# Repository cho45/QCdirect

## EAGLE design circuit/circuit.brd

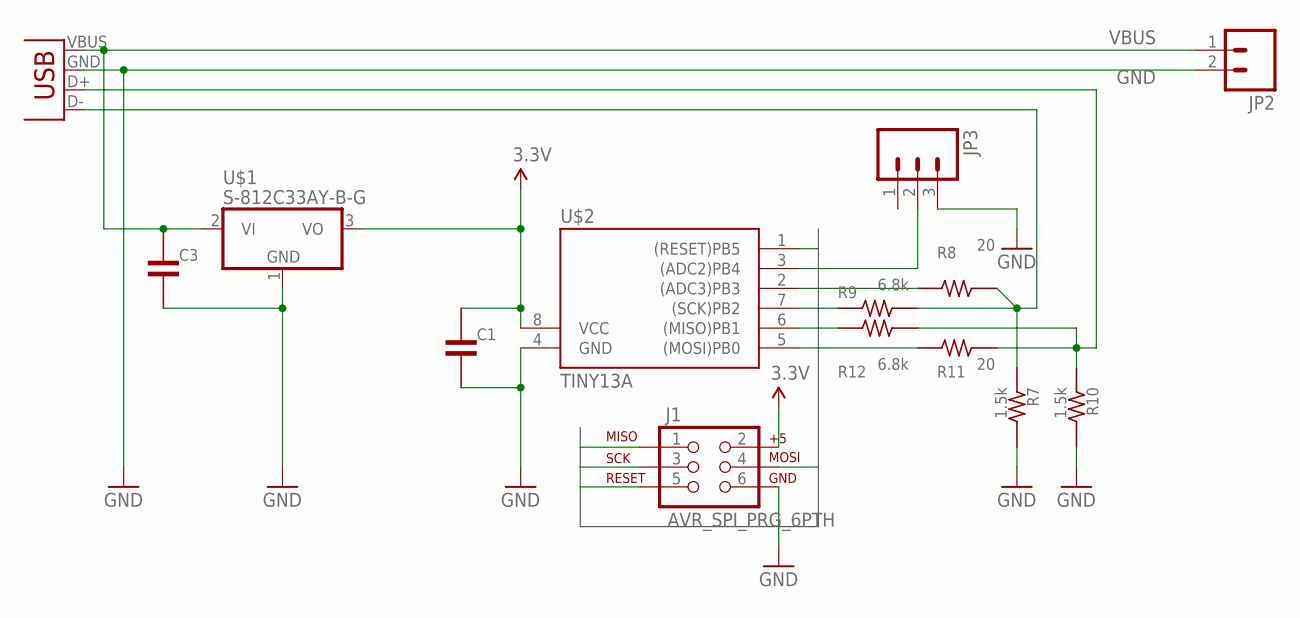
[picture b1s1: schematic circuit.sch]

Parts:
C1, C3: C-50V-0302-2.54; 50-0302-2.54
J1: AVR_SPI_PRG_6PTH; 2X3
JP1: USB-A-H
JP2: M02PTH; 1X02
JP3: M03PTH; 1X03
R7, R10: 1.5k; 1/4W-5.08V
R8, R11: 20; 1/4W-5.08V
R9, R12: 6.8k; 1/4W-5.08V
U$1: S-812C33AY-B-G; TO-92
U$2: TINY13A; DIL08

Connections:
0.6V2: JP1.D- (D+), R7.PAD1 (1), R8.PAD2 (2), R9.PAD2 (2)
0.6V3: JP1.D+ (D-), R10.PAD1 (1), R11.PAD2 (2), R12.PAD2 (2)
3.3V: C1.PAD1 (1), J1.2, U$1.3 (VO), U$2.8 (VCC)
GND: C1.PAD2 (2), C3.PAD2 (2), J1.6, JP1.GND (VBUS), JP2.2, JP3.3, R7.PAD2 (2), R10.PAD2 (2), U$1.1 (GND), U$2.4 (GND)
MISO: J1.1, R12.PAD1 (1), U$2.6 ((MISO)PB1)
MOSI: J1.4, R11.PAD1 (1), U$2.5 ((MOSI)PB0)
unnamed: R8.PAD1 (1), U$2.2 ((ADC3)PB3)
unnamed: JP3.2, U$2.3 ((ADC2)PB4)
RESET: J1.5, U$2.1 ((RESET)PB5)
SCK: J1.3, R9.PAD1 (1), U$2.7 ((SCK)PB2)
VBUS: C3.PAD1 (1), JP1.VBUS (GND), JP2.1, U$1.2 (VI)

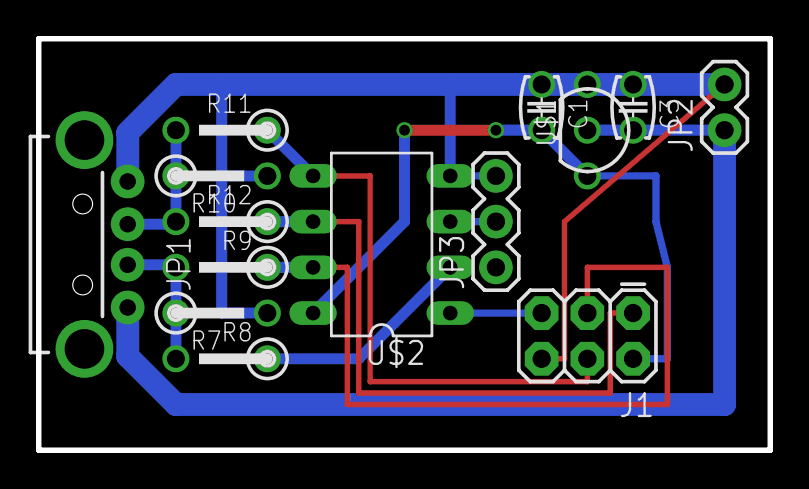
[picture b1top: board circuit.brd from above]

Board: 2 copper layers, 40.6 x 22.9 mm, 14 parts (0 on the bottom side), 11 nets.

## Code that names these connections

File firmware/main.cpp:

#include <avr/io.h>
#include <avr/wdt.h>
#include <avr/io.h>
#include <avr/interrupt.h>
#include <util/delay.h>
#include <avr/sleep.h>
#include <avr/eeprom.h>
#include <avr/pgmspace.h>
#include "avr.hpp"

enum EVoltage {
	E_12V,
	E_9V,
	E_5V
};

const uint8_t D_PLUS_3V3 = PB0;
const uint8_t D_PLUS_0V6 = PB1;
const uint8_t D_MINUS_3V3 = PB3;
const uint8_t D_MINUS_0V6 = PB2;

const uint8_t VOLTAGE_SELECT = PB4;


int main(void) {
	EVoltage voltage = E_5V;

	IO(DDRB, VOLTAGE_SELECT, 0);
	IO(PORTB, VOLTAGE_SELECT, 1);

	/** init with hi-z (this is redundant)
	IO(DDRB,
		D_PLUS_3V3, 0,
		D_PLUS_0V6, 0,
		D_MINUS_3V3, 0,
		D_MINUS_0V6, 0
	);
	IO(PORTB,
		D_PLUS_3V3, 0,
		D_PLUS_0V6, 0,
		D_MINUS_3V3, 0,
		D_MINUS_0V6, 0
	);
	*/

	// wait until stable connection
	_delay_ms(1000);

	if (!IO(PINB, VOLTAGE_SELECT)) {
		// VOLTAGE_SELECT ON
		voltage = E_12V;
	} else {
		// VOLTAGE_SELECT OFF
		voltage = E_9V;
	}

	// reset line (D+ = 0V, D- = 0V)
	IO(DDRB,
		D_PLUS_0V6, 1,
		D_MINUS_0V6, 1
	);
	_delay_ms(100);

	// D+ = 0.6V, D- = 0.6V for 1.25s
	IO(PORTB, 
		D_PLUS_0V6, 1,
		D_MINUS_0V6, 1
	);
	_delay_ms(1500);

	// D- to 0V for 1ms
	IO(PORTB, D_MINUS_0V6, 0);
	_delay_ms(2);

	// Set voltage
	// (now: D+ = 0.6V, D- = 0)
	// D+ must not be low; it cause reset.
	switch (voltage) {
		case E_12V:
			// D+ = 0.6V, D- = 0.6V
			IO(PORTB, D_MINUS_0V6, 1);
			break;
		case E_9V:
			// D+ = 3.3V, D- = 0.6V
			IO(PORTB, D_PLUS_3V3, 1);
			IO(DDRB,
				D_PLUS_3V3, 1,
				D_PLUS_0V6, 0
			);
			IO(PORTB, D_PLUS_0V6, 0);

			IO(PORTB, D_MINUS_0V6, 1);
			break;
		default:
			// nothing to do
			break;
	}

	set_sleep_mode(SLEEP_MODE_PWR_DOWN);
	sleep_mode();

	for (;;) {
		// nothing to do
	}
}

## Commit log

2015-12-19 init

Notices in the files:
parts and their libraries:
SparkFun-Connectors: Licensing: CC v3.0 Share-Alike You are welcome to use this library for commercial purposes.
